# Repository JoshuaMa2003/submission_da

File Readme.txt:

Student Name: Joshua Martinez

Student #: 5007531628

Student Email: marti87@unlv.nevada.edu

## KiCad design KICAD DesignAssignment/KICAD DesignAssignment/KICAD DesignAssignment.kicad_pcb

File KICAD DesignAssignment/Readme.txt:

Student Name: Joshua Martinez
 
Student #: 5007531628

Student Email: marti87@unlv.nevada.edu

Primary Github Address: https://github.com/JoshuaMa2003

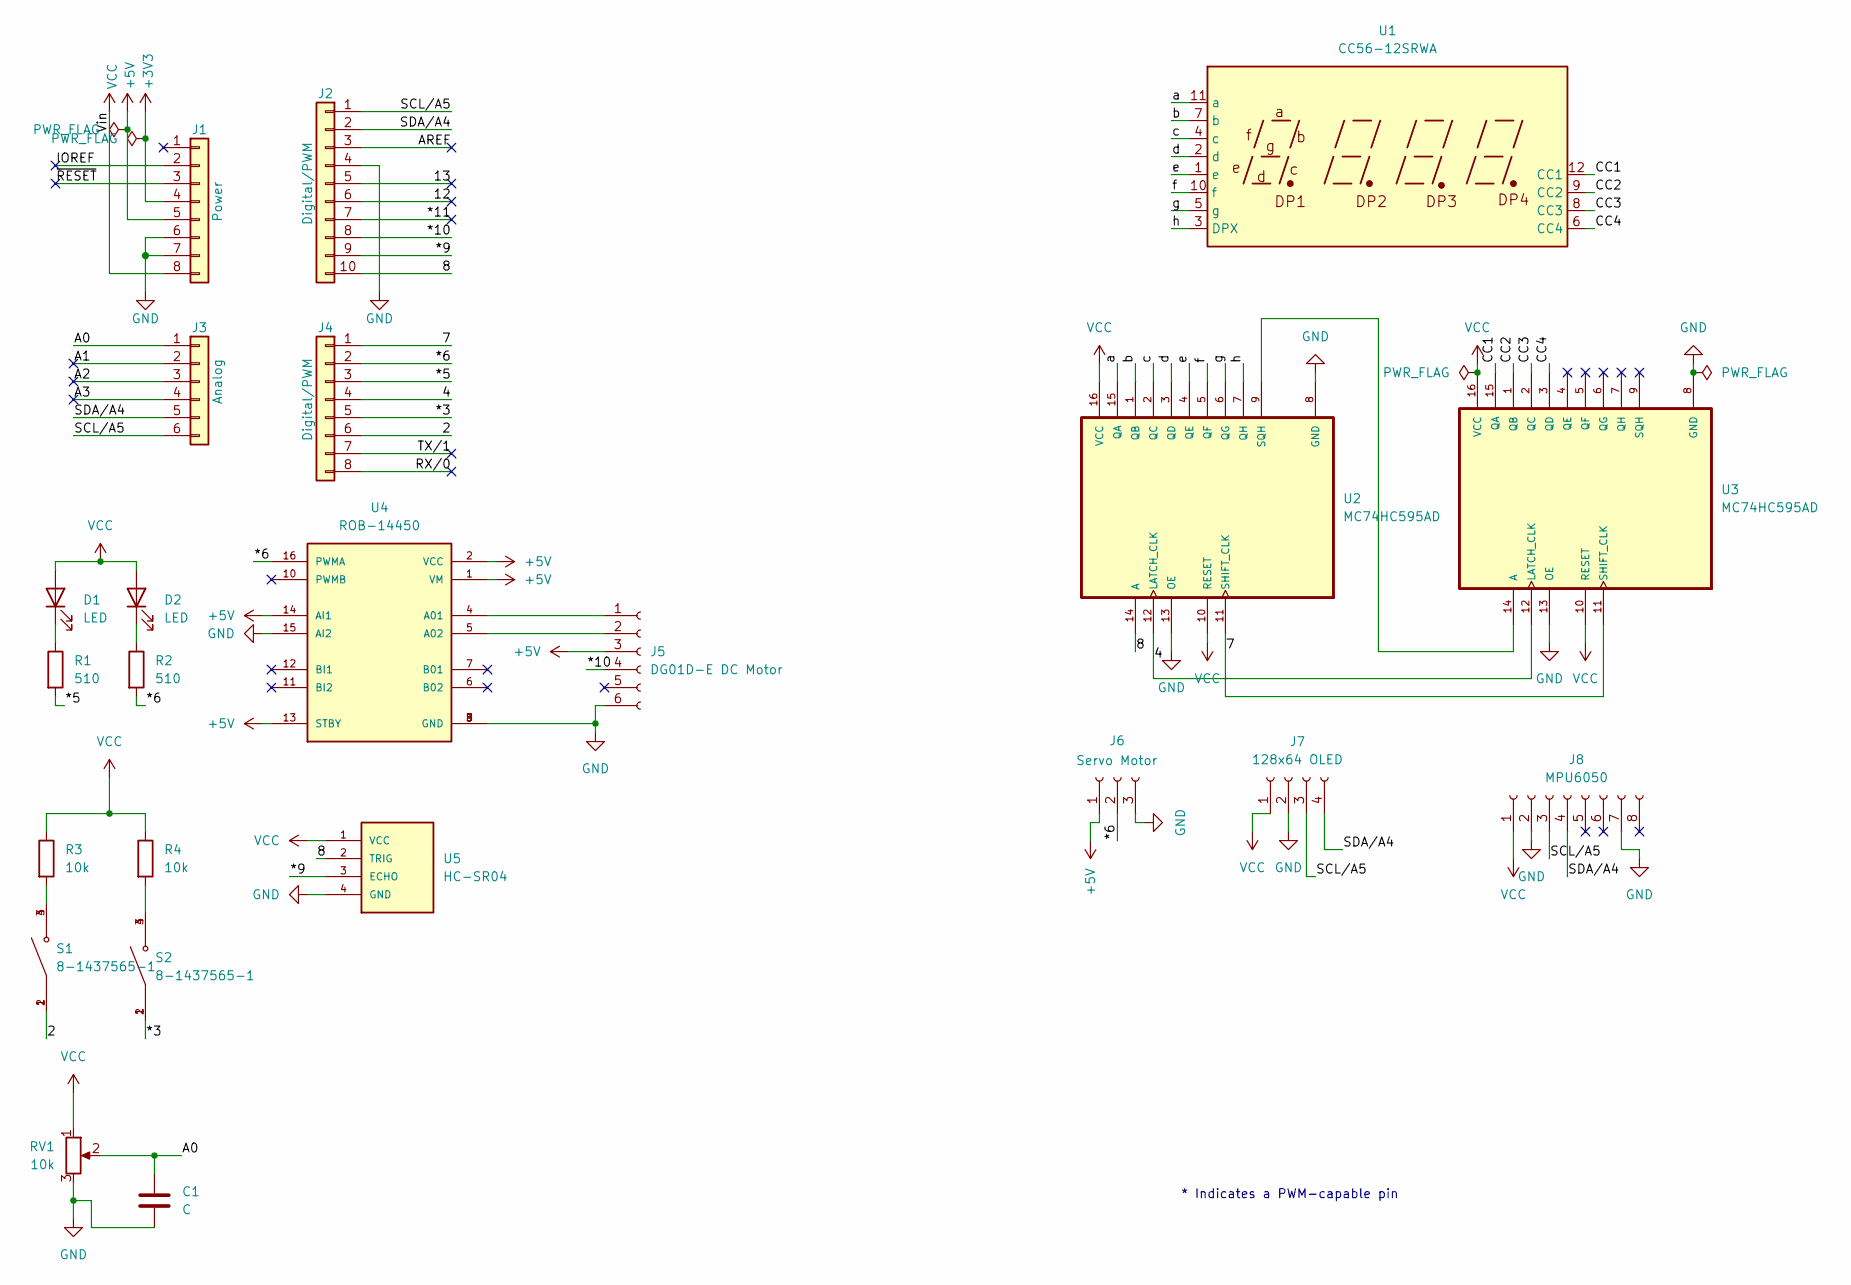
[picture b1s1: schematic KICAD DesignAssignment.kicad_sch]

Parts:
C1: C; C_Radial_D4.0mm_H7.0mm_P1.50mm
D1, D2: LED; LED_D3.0mm
J1: Power; PinSocket_1x08_P2.54mm_Vertical
J2: Digital/PWM; PinSocket_1x10_P2.54mm_Vertical
J3: Analog; PinSocket_1x06_P2.54mm_Vertical
J4: Digital/PWM; PinSocket_1x08_P2.54mm_Vertical
J5: DG01D-E DC Motor; PinHeader_1x04_P2.54mm_Vertical
J6: Servo Motor; PinHeader_1x04_P2.54mm_Vertical
J7: 128x64 OLED; PinHeader_1x04_P2.54mm_Vertical
J8: MPU6050; PinHeader_1x04_P2.54mm_Vertical
R1, R2: 510; R_Axial_DIN0204_L3.6mm_D1.6mm_P2.54mm_Vertical
R3, R4: 10k; R_Axial_DIN0204_L3.6mm_D1.6mm_P2.54mm_Vertical
RV1: 10k; Potentiometer_Vishay_T73YP_Vertical
S1, S2: 8-1437565-1; SW_8-1437565-1; PARTREV H3
U1: CC56-12SRWA; CA56-12SRWA
U2, U3: MC74HC595AD; SOIC127P600X175-16N
U4: ROB-14450; MODULE_ROB-14450; PARTREV 11-13-17; DigiKey_Part_Number 1568-1755-ND
U5: HC-SR04; XCVR_HC-SR04

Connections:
+3V3: J1.4
+5V: J1.5, J5.3, J6.1, U4.1 (VM), U4.2 (VCC), U4.13 (STBY), U4.14 (AI1)
/2: J4.6, S1.1, S1.2
/4: J4.4, U2.12 (LATCH_CLK), U3.12 (LATCH_CLK)
/7: J4.1, U2.11 (SHIFT_CLK), U3.11 (SHIFT_CLK)
/8: J2.10, U2.14 (A), U5.2 (TRIG)
/12: J2.6
/13: J2.5
/*3: J4.5, S2.1, S2.2
/*5: J4.3, R1.2
/*6: J4.2, J6.2, R2.2, U4.16 (PWMA)
/*9: J2.9, U5.3 (ECHO)
/*10: J2.8, J5.4
/*11: J2.7
/A0: C1.1, J3.1, RV1.2
/A1: J3.2
/A2: J3.3
/A3: J3.4
/AREF: J2.3
/CC1: U1.12 (CC1), U3.15 (QA)
/CC2: U1.9 (CC2), U3.1 (QB)
/CC3: U1.8 (CC3), U3.2 (QC)
/CC4: U1.6 (CC4), U3.3 (QD)
/IOREF: J1.2
/RX/0: J4.8
/SCL/A5: J2.1, J3.6, J7.3, J8.3
/SDA/A4: J2.2, J3.5, J7.4, J8.4
/TX/1: J4.7
/a: U1.11 (a), U2.15 (QA)
/b: U1.7 (b), U2.1 (QB)
/c: U1.4 (c), U2.2 (QC)
/d: U1.2 (d), U2.3 (QD)
/e: U1.1 (e), U2.4 (QE)
/f: U1.10 (f), U2.5 (QF)
/g: U1.5 (g), U2.6 (QG)
/h: U1.3 (DPX), U2.7 (QH)
/~RESET: J1.3
GND: C1.2, J1.6, J1.7, J2.4, J5.6, J6.3, J7.2, J8.2, J8.7, RV1.3, U2.8 (GND), U2.13 (OE), U3.8 (GND), U3.13 (OE), U4.3 (GND), U4.8 (GND), U4.9 (GND), U4.15 (AI2), U5.4 (GND)
unnamed: D1.1 (K), R1.1
unnamed: D2.1 (K), R2.1
unnamed: J5.1, U4.4 (A01)
unnamed: J5.2, U4.5 (A02)
unnamed: R3.2, S1.3, S1.4
unnamed: R4.2, S2.3, S2.4
unnamed: U2.9 (SQH), U3.14 (A)
VCC: D1.2 (A), D2.2 (A), J1.8, J7.1, J8.1, R3.1, R4.1, RV1.1, U2.10 (RESET), U2.16 (VCC), U3.10 (RESET), U3.16 (VCC), U5.1 (VCC)

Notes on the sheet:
* Indicates a PWM-capable pin

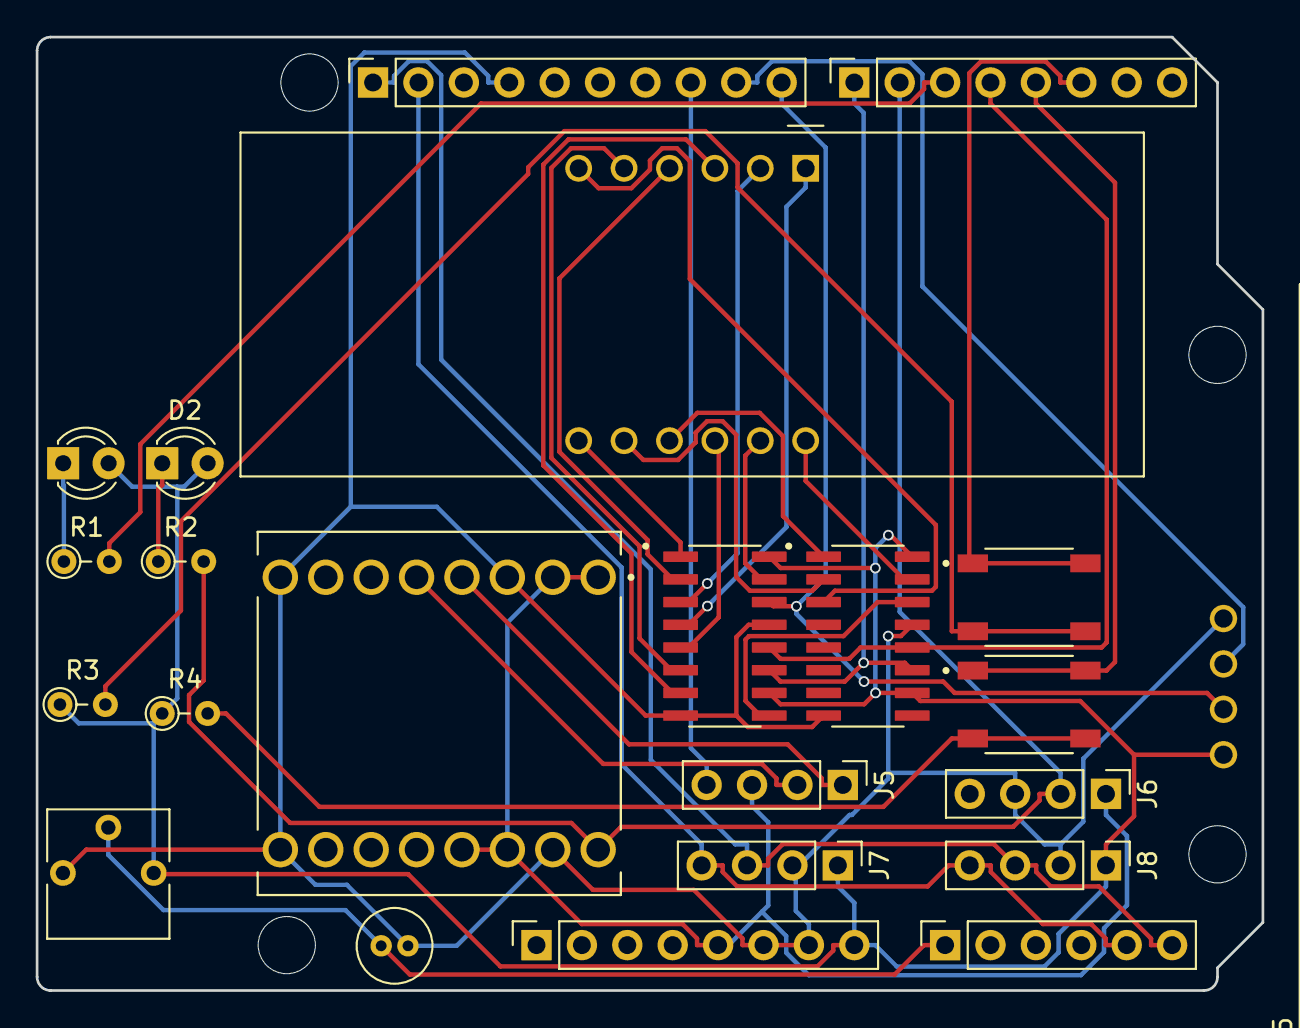
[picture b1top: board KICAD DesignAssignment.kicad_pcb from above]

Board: 2 copper layers, 68.6 x 53.3 mm, 27 parts (0 on the bottom side), 34 nets.

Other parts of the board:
MH1, MH2, MH3, MH4: MountingHole_3.2mm

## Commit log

2024-02-26 Add files via upload
    Design Assignment 1 Upload
